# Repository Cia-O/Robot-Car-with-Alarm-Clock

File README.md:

# Robot-Car-with-Alarm-Clock
This is a moving alarm clock  repository, that will features as much as we can schematics and code

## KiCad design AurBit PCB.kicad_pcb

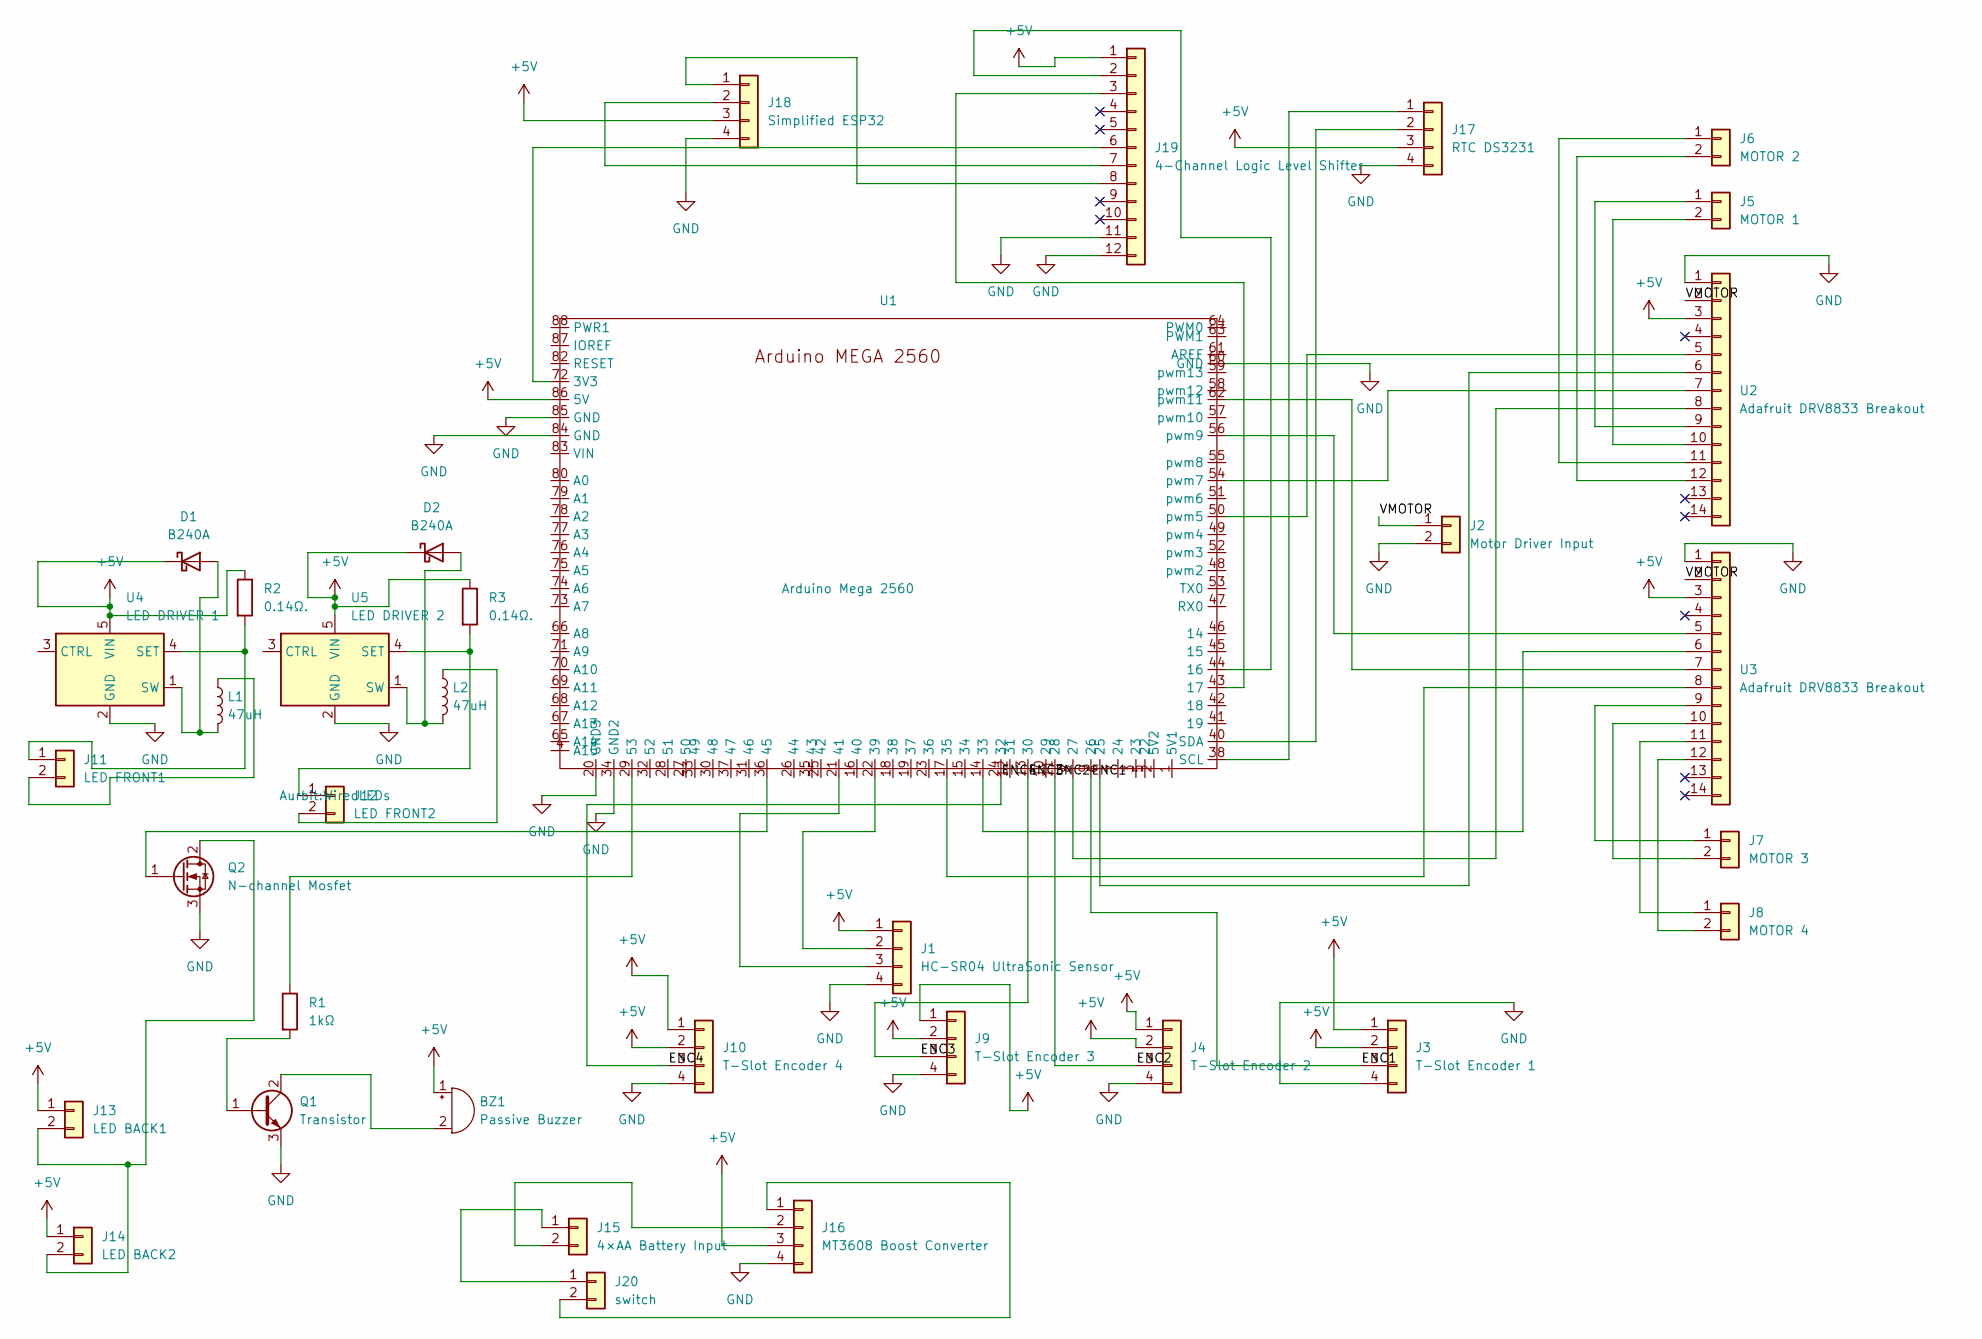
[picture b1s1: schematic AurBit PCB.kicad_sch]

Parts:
BZ1: Passive Buzzer; PassiveBuzzer_AD319
D1, D2: B240A; D_SMB_Handsoldering
J1: HC-SR04 UltraSonic Sensor; Wired_Solder_4Pins
J2: Motor Driver Input
J3: T-Slot Encoder 1; Wired_Solder_4Pins
J4: T-Slot Encoder 2; Wired_Solder_4Pins
J5: MOTOR 1; WiredLEDs
J6: MOTOR 2; WiredLEDs
J7: MOTOR 3; WiredLEDs
J8: MOTOR 4; WiredLEDs
J9: T-Slot Encoder 3; Wired_Solder_4Pins
J10: T-Slot Encoder 4; Wired_Solder_4Pins
J11: LED FRONT1; WiredLEDs
J12: LED FRONT2; WiredLEDs
J13: LED BACK1; WiredLEDs
J14: LED BACK2; WiredLEDs
J15: 4×AA Battery Input; WiredLEDs
J16: MT3608 Boost Converter; Wired_Solder_4Pins
J17: RTC DS3231; Wired_Solder_4Pins
J18: Simplified ESP32; Wired_Solder_4Pins
J19: 4-Channel Logic Level Shifter; Logic_Level_Converter_AD227
J20: switch; WiredLEDs
L1, L2: 47uH; CODACA_SPRH74_7.3x7.3mm
Q1: Transistor; TO-92_Inline_Wide
Q2: N-channel Mosfet; TO-220-3_Vertical
R1: 1kΩ; WiredLEDs
R2, R3: 0.14Ω.; WiredLEDs
U1: Arduino Mega 2560; AurBit_Arduino_Mega_2560_R3
U2, U3: Adafruit DRV8833 Breakout; DRV8833-footprint
U4: LED DRIVER 1; SOT-23-5_HandSoldering
U5: LED DRIVER 2; SOT-23-5_HandSoldering

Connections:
+5V: BZ1.1 (+), D1.1 (K), D2.1 (K), J1.1 (VCC), J3.1 (+), J3.2 (L), J4.1 (+), J4.2 (L), J9.1 (+), J9.2 (L), J10.1 (+), J10.2 (L), J13.1 (+), J14.1 (+), J16.3 (VOUT+), J17.3 (VCC), J18.3 (GND), J19.1 (HV), R2.1, R3.1, U1.86 (5V), U2.3 (SLP), U3.3 (SLP), U4.5 (VIN), U5.5 (VIN)
/ENC1: J3.3 (OUT), U1.9 (26)
/ENC2: J4.3 (OUT), U1.11 (28)
/ENC3: J9.3 (OUT), U1.13 (30)
/ENC4: J10.3 (OUT), U1.24 (32)
/VMOTOR: J2.1 (VMOTOR+), U2.2 (VM), U3.2 (VM)
GND: J1.4 (GND), J2.2 (GND), J3.4 (-), J4.4 (-), J9.4 (-), J10.4 (-), J16.4 (VOUT-), J17.4 (GND), J18.4 (VBUS(5V)), J19.11 (GND), J19.12 (GND), Q1.3 (E), Q2.3 (S), U1.20 (GND3), U1.34 (GND2), U1.60 (GND), U1.84 (GND), U1.85 (GND), U2.1 (GND), U3.1 (GND), U4.2 (GND), U5.2 (GND)
unnamed: BZ1.2 (-), Q1.2 (C)
unnamed: D1.2 (A), L1.2 (-), U4.1 (SW)
unnamed: D2.2 (A), L2.2 (-), U5.1 (SW)
unnamed: J1.3 (ECHO), U1.21 (41)
unnamed: J1.2 (TRIG), U1.22 (39)
unnamed: J5.1, U2.9 (AOUT1)
unnamed: J5.2, U2.10 (AOUT2)
unnamed: J6.1, U2.11 (BOUT1)
unnamed: J6.2, U2.12 (BOUT2)
unnamed: J7.1, U3.9 (AOUT1)
unnamed: J7.2, U3.10 (AOUT2)
unnamed: J8.1, U3.11 (BOUT1)
unnamed: J8.2, U3.12 (BOUT2)
unnamed: J11.1 (+), R2.2, U4.4 (SET)
unnamed: J11.2 (-), L1.1 (+)
unnamed: J12.1 (+), R3.2, U5.4 (SET)
unnamed: J12.2 (-), L2.1 (+)
unnamed: J13.2 (-), J14.2 (-), Q2.2 (D)
unnamed: J15.1 (+), J20.1
unnamed: J15.2 (-), J16.2 (VIN-)
unnamed: J16.1 (VIN+), J20.2
unnamed: J17.1 (SCL), U1.38 (SCL)
unnamed: J17.2 (SDA), U1.40 (SDA)
unnamed: J18.2 (RX0), J19.7 (LV1)
unnamed: J18.1 (TXO), J19.8 (LV2)
unnamed: J19.2 (HV1), U1.44 (16)
unnamed: J19.3 (HV2), U1.43 (17)
unnamed: J19.6 (LV), U1.72 (3V3)
unnamed: Q1.1 (B), R1.2
unnamed: Q2.1 (G), U1.36 (45)
unnamed: U1.6 (25), U2.6 (AIN2)
unnamed: U1.8 (27), U2.8 (BIN2)
unnamed: U1.14 (33), U3.6 (AIN2)
unnamed: U1.17 (35), U3.8 (BIN2)
unnamed: R1.1, U1.29 (53)
unnamed: U1.50 (pwm5), U2.5 (AIN1)
unnamed: U1.54 (pwm7), U2.7 (BIN1)
unnamed: U1.56 (pwm9), U3.5 (AIN1)
unnamed: U1.62 (pwm11), U3.7 (BIN1)

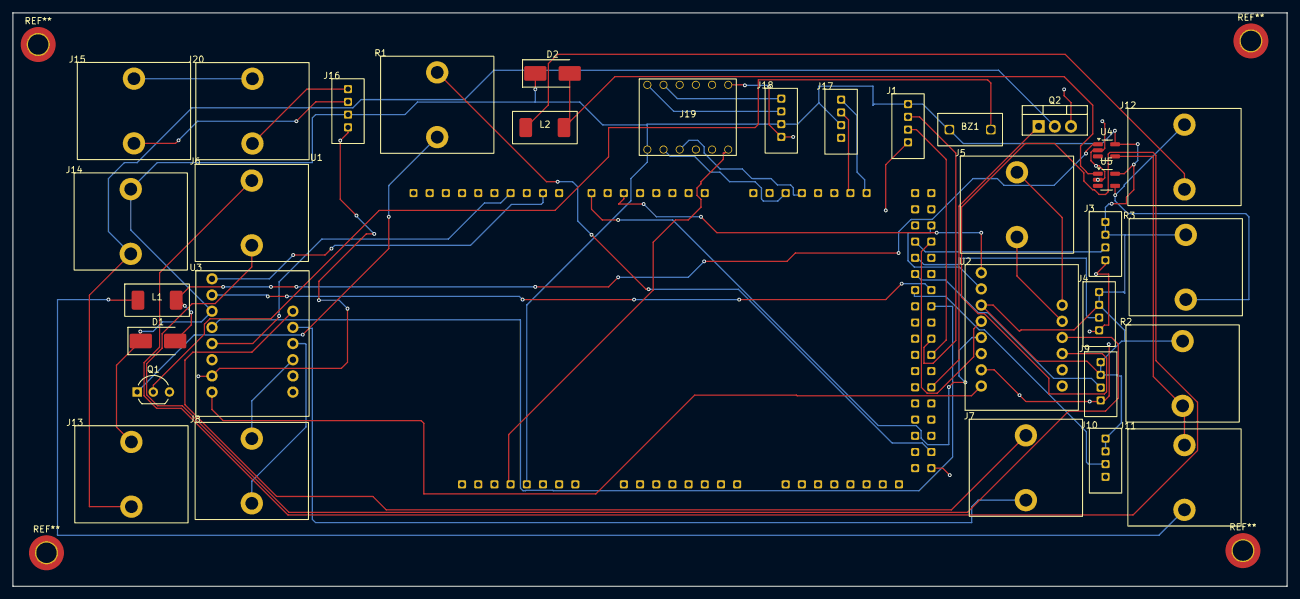
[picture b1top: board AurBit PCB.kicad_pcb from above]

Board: 2 copper layers, 200.0 x 90.0 mm, 34 parts (0 on the bottom side), 46 nets.
